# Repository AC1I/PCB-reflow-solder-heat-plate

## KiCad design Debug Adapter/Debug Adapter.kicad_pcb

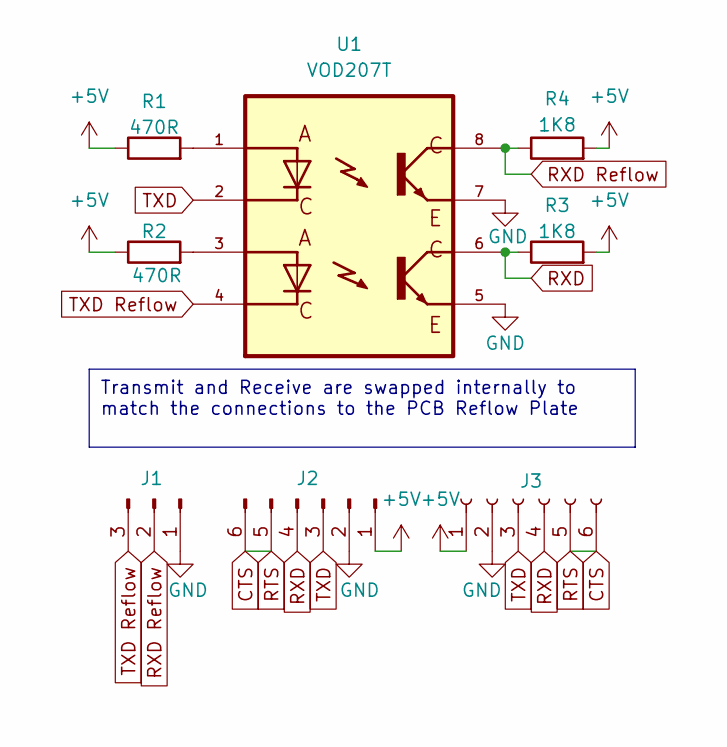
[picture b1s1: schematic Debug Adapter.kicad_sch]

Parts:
J1: Conn_01x03_Pin; PinHeader_1x03_P2.54mm_Vertical
J2: Conn_01x06_Pin; PinHeader_1x06_P2.54mm_Vertical
J3: Conn_01x06_Socket; PinHeader_1x06_P2.54mm_Horizontal
R1, R2: 470R; R_0402_1005Metric
R3, R4: 1K8; R_0402_1005Metric
U1: VOD207T; SOIC127P610X331-8N

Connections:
+5V: J2.1, J3.1, R1.1, R2.1, R3.2, R4.2
CTS: J2.5, J2.6, J3.5, J3.6
GND: J1.1, J2.2, J3.2, U1.5, U1.7
unnamed: R1.2, U1.1
unnamed: R2.2, U1.3
RXD: J2.4, J3.4, R3.1, U1.6
RXD Reflow: J1.2, R4.1, U1.8
TXD: J2.3, J3.3, U1.2
TXD Reflow: J1.3, U1.4

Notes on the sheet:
Transmit and Receive are swapped internally to match the connections to the PCB Reflow Plate

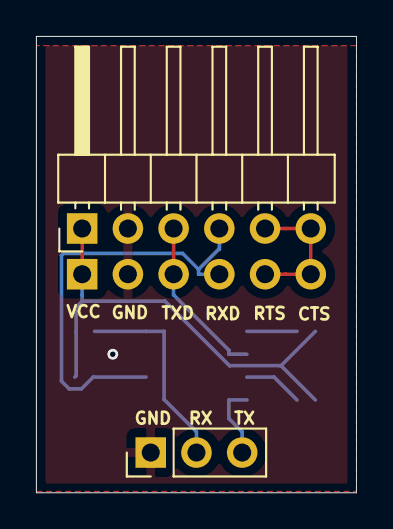
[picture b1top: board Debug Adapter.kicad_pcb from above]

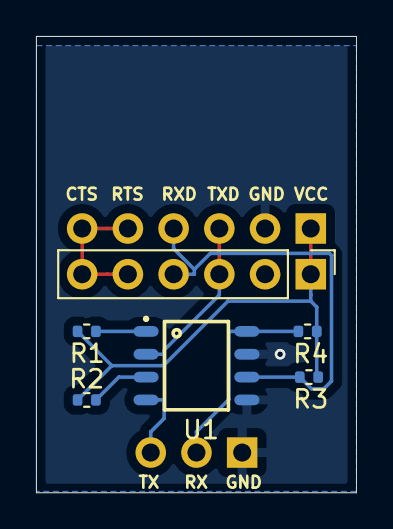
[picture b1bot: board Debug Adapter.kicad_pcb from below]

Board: 2 copper layers, 17.8 x 25.3 mm, 8 parts (6 on the bottom side), 9 nets.

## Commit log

2024-09-28 Fix read of bed resistance from EEPROM
2024-09-28 Manage maximum current hack
    We need to keep the current below 5A, or we blow the fuse. There is no current shunt, but there is a voltage input. Added hack (gimmick) to keep the current from exceeding 5 amps
2024-09-28 Opps
    Fix malconstructed comment.
2024-09-29 Add user configurable PWM max duty cycle
    If the resistance of the PCB does not raise as expected when heated, or is to low when started the board will draw in excess of 5 amps and blow the fuse. Added a user configurable variable to limit t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
2024-09-29 Constant current mode
    When the PWM maximum duty cycle constraint is 0 enable constant current mode.
2024-10-07 Improved Temperature calculations
    Utilized the temperature translation table from the LMT85 datasheet.
    Added serial debug interface.
    Create CSV file of temperature difference between temp1 and temp2 sensor.
    Added different led colors to indicate heating, cooldown, ready states.
    Added fork specific readme.
2024-10-11 Tweak Temperature Calibration
2024-10-17 Correct Debug Adapter
2024-10-25 Update temperature estimate
2024-11-06 More temperature adjustments
2024-11-06 Update Serial Commands
